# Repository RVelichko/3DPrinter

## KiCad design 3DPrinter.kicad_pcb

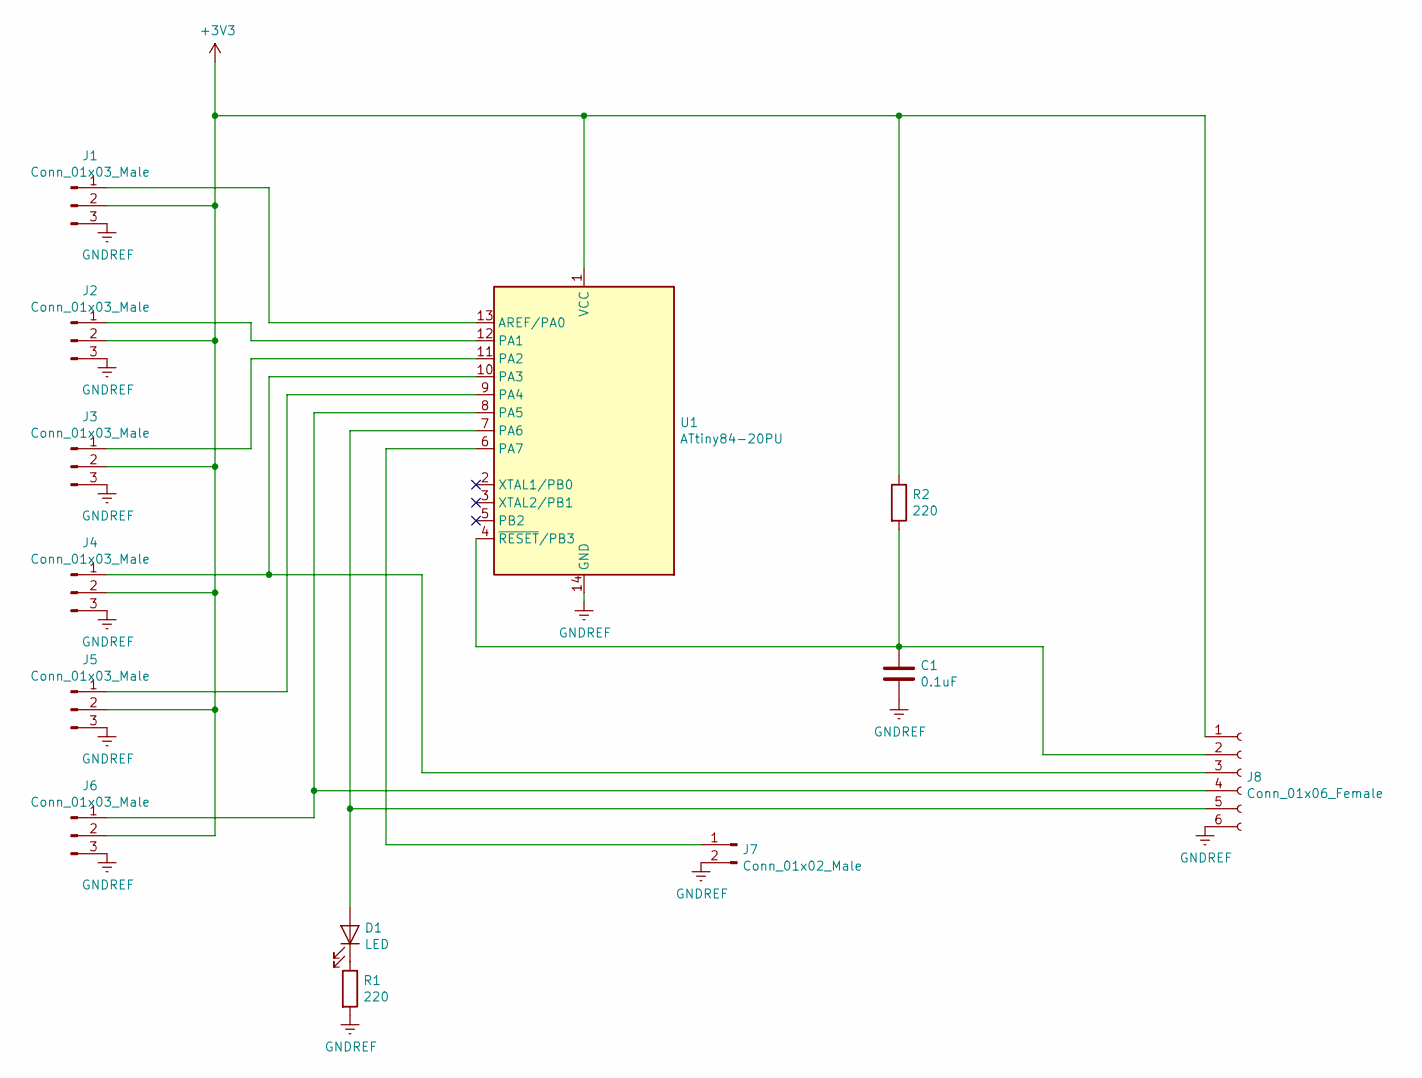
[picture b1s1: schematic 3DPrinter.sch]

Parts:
C1: 0.1uF; C_Disc_D3.0mm_W1.6mm_P2.50mm
D1: LED; LED_D3.0mm
J1, J2, J3, J4, J5, J6: Conn_01x03_Male; PinHeader_1x03_P2.54mm_Horizontal
J7: Conn_01x02_Male; PinHeader_1x02_P2.54mm_Horizontal
J8: Conn_01x06_Female; PinSocket_1x06_P1.00mm_Vertical
R1, R2: 220; R_Axial_DIN0204_L3.6mm_D1.6mm_P5.08mm_Horizontal
U1: ATtiny84-20PU; DIP-14_W7.62mm

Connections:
+3V3: J1.2, J2.2, J3.2, J4.2, J5.2, J6.2, J8.1, R2.1, U1.1 (VCC)
GNDREF: C1.2, J1.3, J2.3, J3.3, J4.3, J5.3, J6.3, J7.2, J8.6, R1.2, U1.14 (GND)
unnamed: C1.1, J8.2, R2.2, U1.4 (~RESET~/PB3)
unnamed: D1.1 (K), R1.1
unnamed: D1.2 (A), J8.5, U1.7 (PA6)
unnamed: J1.1, U1.13 (AREF/PA0)
unnamed: J2.1, U1.12 (PA1)
unnamed: J3.1, U1.11 (PA2)
unnamed: J4.1, J8.3, U1.10 (PA3)
unnamed: J5.1, U1.9 (PA4)
unnamed: J6.1, J8.4, U1.8 (PA5)
unnamed: J7.1, U1.6 (PA7)

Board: 2 copper layers, 13 parts (0 on the bottom side), 12 nets, no tracks yet.

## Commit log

2021-08-30 Добавлено крепление моторов экструдеров.
2021-09-02 Добавлен подвес эффектора.
2021-09-08 Исправлена главная высота рамы эффектора.
